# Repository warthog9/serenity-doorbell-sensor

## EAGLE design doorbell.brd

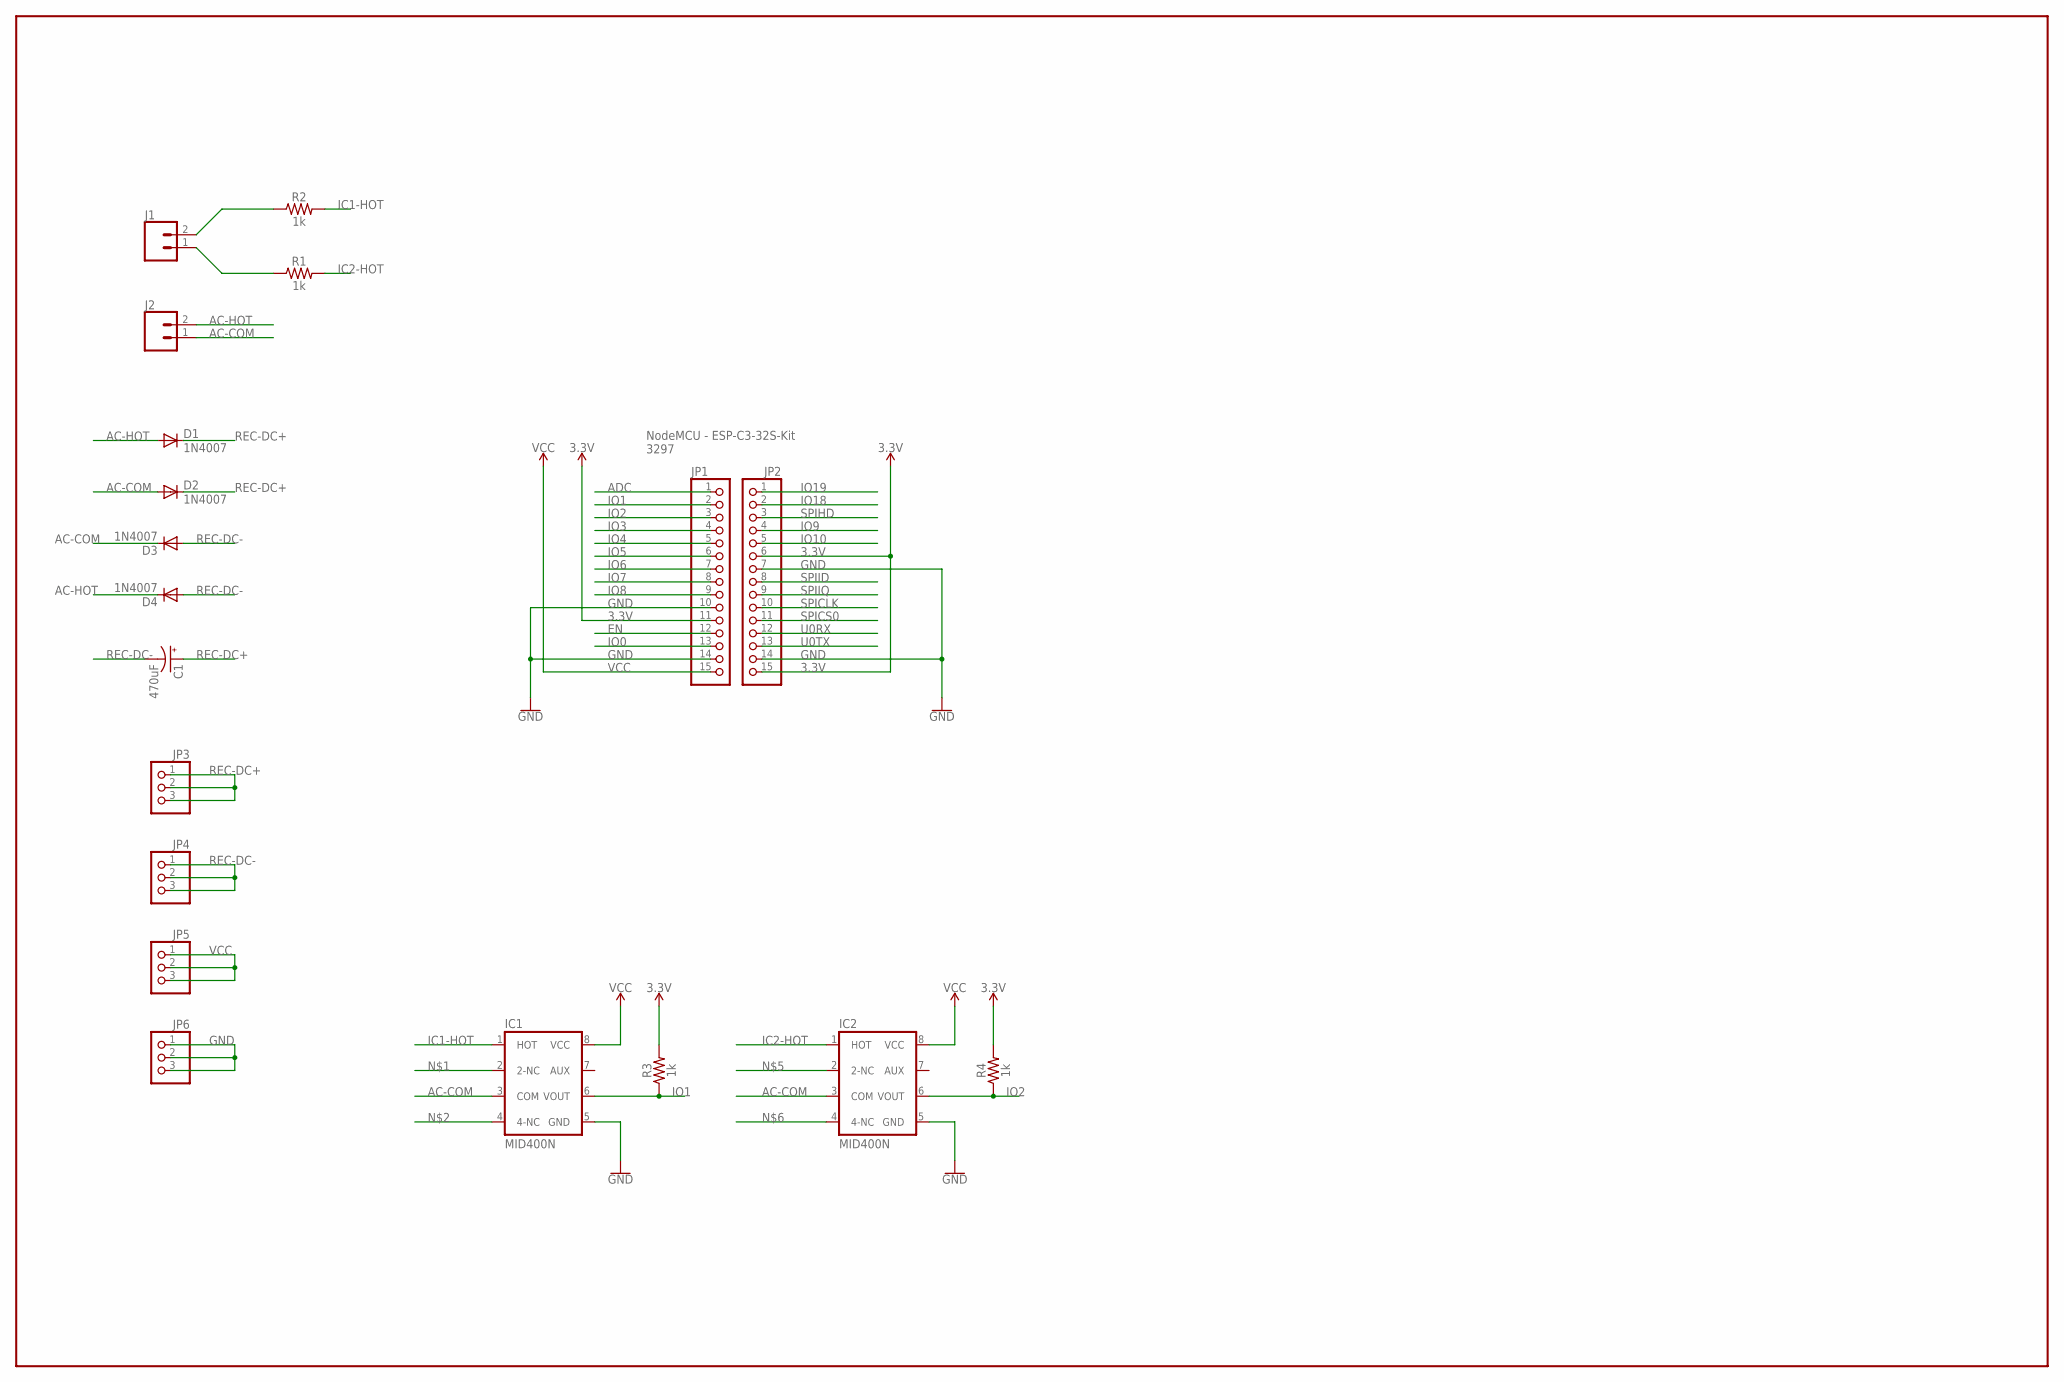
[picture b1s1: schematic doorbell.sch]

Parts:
C1: 470uF; E7,5-18
D1, D2, D3, D4: 1N4007; DO41-10
IC1, IC2: MID400N; DIL08-ROUND
J1, J2: CONN_023.5MM; SCREWTERMINAL-3.5MM-2
JP1, JP2: PINHD-1X15; 1X15
JP3, JP4, JP5, JP6: PINHD-1X3; 1X03
R1, R2, R3, R4: 1k; AXIAL-0.3

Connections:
3.3V: JP1.11, JP2.6, JP2.15, R3.P$2 (2), R4.P$2 (2)
AC-COM: D2.A, D3.C, IC1.3 (COM), IC2.3 (COM), J2.1
AC-HOT: D1.A, D4.C, J2.2
ADC: JP1.1
EN: JP1.12
GND: IC1.5 (GND), IC2.5 (GND), JP1.10, JP1.14, JP2.7, JP2.14, JP6.1, JP6.2, JP6.3
IC1-HOT: IC1.1 (HOT), R2.P$2 (2)
IC2-HOT: IC2.1 (HOT), R1.P$2 (2)
IO0: JP1.13
IO1: IC1.6 (VOUT), JP1.2, R3.P$1 (1)
IO2: IC2.6 (VOUT), JP1.3, R4.P$1 (1)
IO3: JP1.4
IO4: JP1.5
IO5: JP1.6
IO6: JP1.7
IO7: JP1.8
IO8: JP1.9
IO9: JP2.4
IO10: JP2.5
IO18: JP2.2
IO19: JP2.1
unnamed: J1.1, R1.P$1 (1)
unnamed: J1.2, R2.P$1 (1)
REC-DC+: C1.+, D1.C, D2.C, JP3.1, JP3.2, JP3.3
REC-DC-: C1.-, D3.A, D4.A, JP4.1, JP4.2, JP4.3
SPICLK: JP2.10
SPICS0: JP2.11
SPIHD: JP2.3
SPIID: JP2.8
SPIIQ: JP2.9
U0RX: JP2.12
U0TX: JP2.13
VCC: IC1.8 (VCC), IC2.8 (VCC), JP1.15, JP5.1, JP5.2, JP5.3

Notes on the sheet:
NodeMCU - ESP-C3-32S-Kit 3297

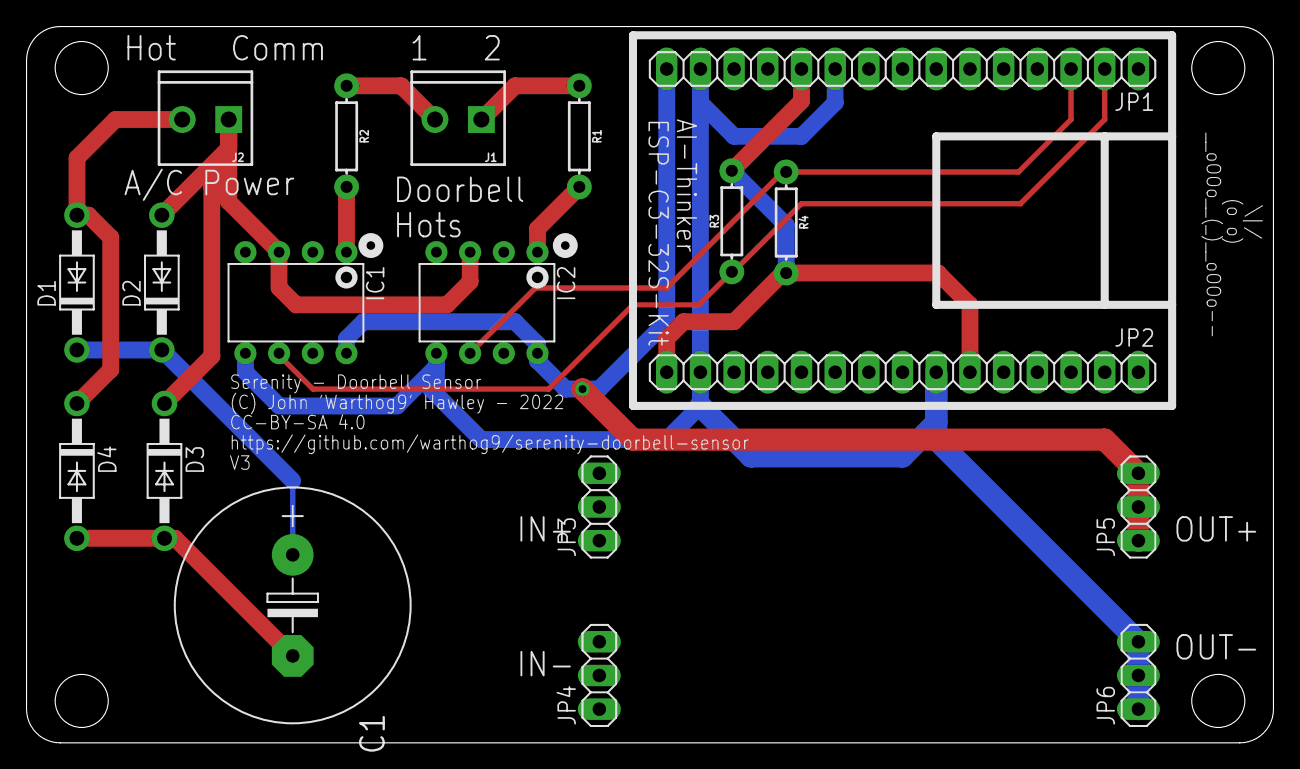
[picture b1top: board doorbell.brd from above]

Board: 2 copper layers, 94.0 x 54.0 mm, 19 parts (0 on the bottom side), 13 nets.

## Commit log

2022-11-15 Initial commit
    This is v3 which should be good for anyone else to
    actually build vs. v2 which needed a minor drill work and a bit of a
    bodge to work around

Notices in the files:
doorbell.brd:
CC-BY-SA 4.0
parts and their libraries:
SparkFun-Connectors: Licensing: Creative Commons ShareAlike 4.0 International - https://creativecommons.org/licenses/by-sa/4.0
